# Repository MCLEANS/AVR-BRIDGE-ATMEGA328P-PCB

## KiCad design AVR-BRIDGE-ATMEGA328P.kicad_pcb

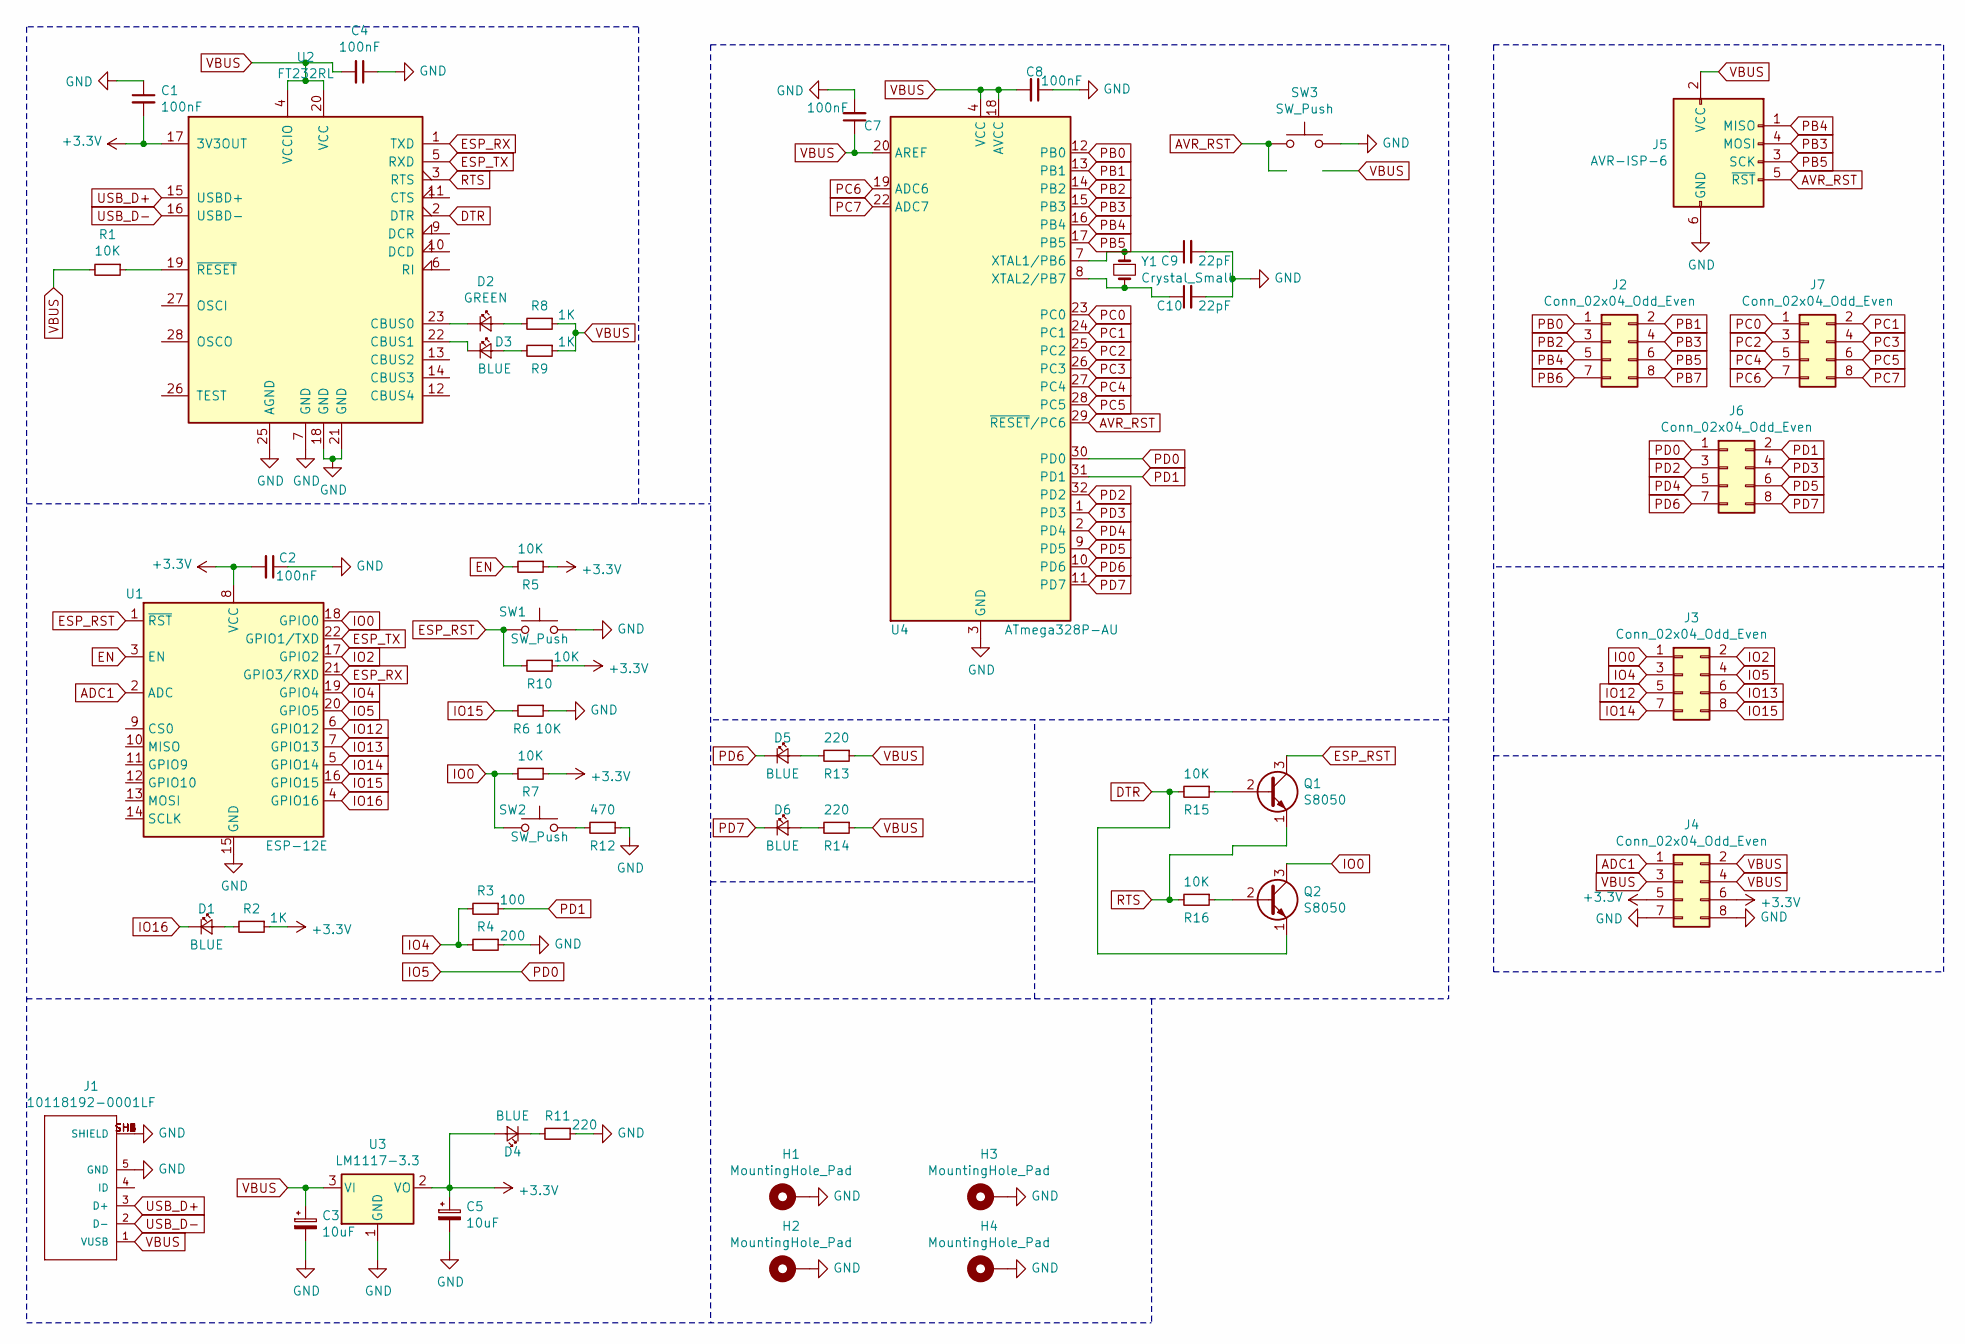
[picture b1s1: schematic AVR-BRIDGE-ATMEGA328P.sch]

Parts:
C1, C2, C4, C7, C8: 100nF; C_0805_2012Metric
C3, C5: 10uF; CP_Elec_4x5.3
C9, C10: 22pF; C_0805_2012Metric
D1, D3, D4, D5, D6: BLUE; LED_0805_2012Metric
D2: GREEN; LED_0805_2012Metric
H1, H2, H3, H4: MountingHole_Pad; MountingHole_2.7mm_Pad_Via
J1: 10118192-0001LF; AMPHENOL_10118192-0001LF
J2, J3, J4, J6, J7: Conn_02x04_Odd_Even; PinHeader_2x04_P2.54mm_Horizontal
J5: AVR-ISP-6; PinHeader_2x03_P2.54mm_Vertical
Q1, Q2: S8050; SOT-23-3
R1, R5, R6, R7, R10, R15, R16: 10K; R_0805_2012Metric
R2, R8, R9: 1K; R_0805_2012Metric
R3: 100; R_0805_2012Metric
R4: 200; R_0805_2012Metric
R11, R13, R14: 220; R_0805_2012Metric
R12: 470; R_0805_2012Metric
SW1, SW2, SW3: SW_Push; Switch_Tactile_SMD_6x6mm_PTS645
U1: ESP-12E
U2: FT232RL; SSOP-28_5.3x10.2mm_P0.65mm
U3: LM1117-3.3; SOT-223
U4: ATmega328P-AU; TQFP-32_7x7mm_P0.8mm
Y1: Crystal_Small; Crystal_SMD_HC49-SD

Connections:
+3V3: C1.2, C2.2, C5.1, D4.2 (A), J4.5, J4.6, R2.1, R5.1, R7.1, R10.1, U1.8 (VCC), U2.17 (3V3OUT), U3.2 (VO)
ADC1: J4.1, U1.2 (ADC)
AVR_RST: J5.5 (~RST), SW3.1, U4.29 (~RESET~/PC6)
DTR: Q2.1 (E), R15.2, U2.2 (DTR)
EN: R5.2, U1.3 (EN)
ESP_RST: Q1.3 (C), R10.2, SW1.1, U1.1 (~RST)
ESP_RX: U1.21 (GPIO3/RXD), U2.1 (TXD)
ESP_TX: U1.22 (GPIO1/TXD), U2.5 (RXD)
GND: C1.1, C2.1, C3.2, C4.1, C5.2, C7.2, C8.1, C9.2, C10.2, H1.1, H2.1, H3.1, H4.1, J1.5 (GND), J1.SH1 (SHIELD), J1.SH2 (SHIELD), J1.SH3 (SHIELD), J1.SH4 (SHIELD), J1.SH5 (SHIELD), J1.SH6 (SHIELD), J4.7, J4.8, J5.6 (GND), R4.1, R6.1, R11.1, R12.1, SW1.2, SW3.2, U1.15 (GND), U2.7 (GND), U2.18 (GND), U2.21 (GND), U2.25 (AGND), U3.1 (GND), U4.3 (GND), U4.5 (GND), U4.21 (GND)
IO0: J3.1, Q2.3 (C), R7.2, SW2.1, U1.18 (GPIO0)
IO2: J3.2, U1.17 (GPIO2)
IO4: J3.3, R3.2, R4.2, U1.19 (GPIO4)
IO5: J3.4, J6.1, U1.20 (GPIO5), U4.30 (PD0)
IO12: J3.5, U1.6 (GPIO12)
IO13: J3.6, U1.7 (GPIO13)
IO14: J3.7, U1.5 (GPIO14)
IO15: J3.8, R6.2, U1.16 (GPIO15)
IO16: D1.1 (K), U1.4 (GPIO16)
unnamed: C9.1, U4.7 (XTAL1/PB6), Y1.1
unnamed: C10.1, U4.8 (XTAL2/PB7), Y1.2
unnamed: D1.2 (A), R2.2
unnamed: D2.1 (K), U2.23 (CBUS0)
unnamed: D2.2 (A), R8.2
unnamed: D3.1 (K), U2.22 (CBUS1)
unnamed: D3.2 (A), R9.2
unnamed: D4.1 (K), R11.2
unnamed: D5.2 (A), R13.2
unnamed: D6.2 (A), R14.2
unnamed: Q1.2 (B), R15.1
unnamed: Q2.2 (B), R16.1
unnamed: R1.1, U2.19 (~RESET~)
unnamed: R12.2, SW2.2
PB0: J2.1, U4.12 (PB0)
PB1: J2.2, U4.13 (PB1)
PB2: J2.3, U4.14 (PB2)
PB3: J2.4, J5.4 (MOSI), U4.15 (PB3)
PB4: J2.5, J5.1 (MISO), U4.16 (PB4)
PB5: J2.6, J5.3 (SCK), U4.17 (PB5)
PB6: J2.7
PB7: J2.8
PC0: J7.1, U4.23 (PC0)
PC1: J7.2, U4.24 (PC1)
PC2: J7.3, U4.25 (PC2)
PC3: J7.4, U4.26 (PC3)
PC4: J7.5, U4.27 (PC4)
PC5: J7.6, U4.28 (PC5)
PC6: J7.7, U4.19 (ADC6)
PC7: J7.8, U4.22 (ADC7)
PD1: J6.2, R3.1, U4.31 (PD1)
PD2: J6.3, U4.32 (PD2)
PD3: J6.4, U4.1 (PD3)
PD4: J6.5, U4.2 (PD4)
PD5: J6.6, U4.9 (PD5)
PD6: D5.1 (K), J6.7, U4.10 (PD6)
PD7: D6.1 (K), J6.8, U4.11 (PD7)
RTS: Q1.1 (E), R16.2, U2.3 (RTS)
USB_D+: J1.3 (D+), U2.15 (USBD+)
USB_D-: J1.2 (D-), U2.16 (USBD-)
VBUS: C3.1, C4.2, C7.1, C8.2, J1.1 (VUSB), J4.2, J4.3, J4.4, J5.2 (VCC), R1.2, R8.1, R9.1, R13.1, R14.1, U2.4 (VCCIO), U2.20 (VCC), U3.3 (VI), U4.4 (VCC), U4.6 (VCC), U4.18 (AVCC), U4.20 (AREF)

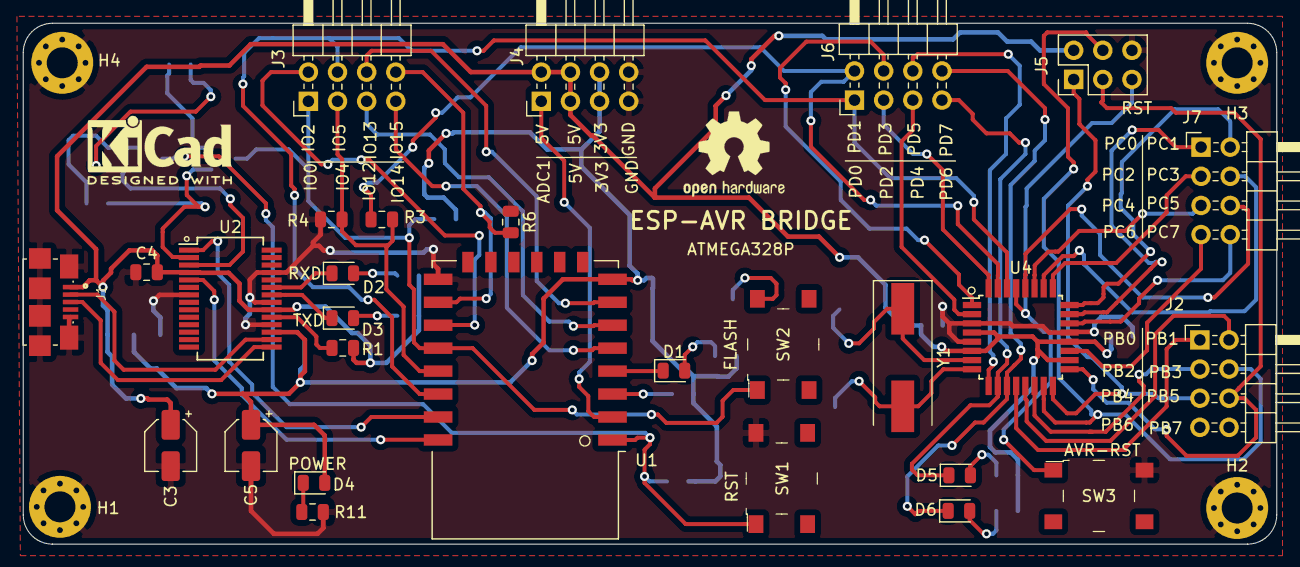
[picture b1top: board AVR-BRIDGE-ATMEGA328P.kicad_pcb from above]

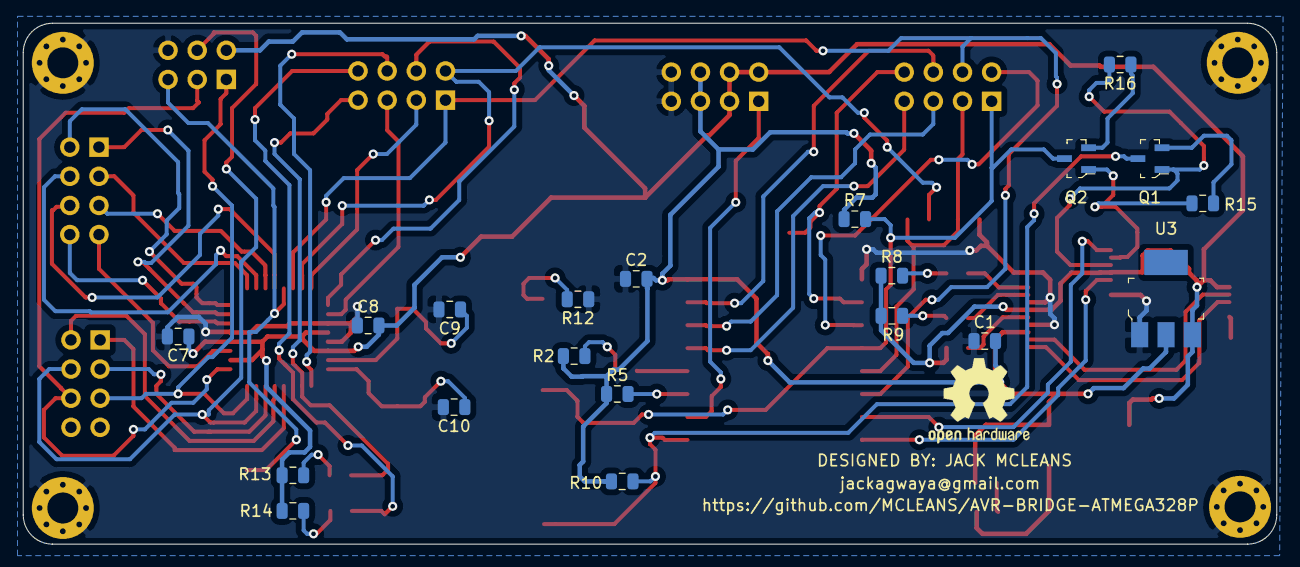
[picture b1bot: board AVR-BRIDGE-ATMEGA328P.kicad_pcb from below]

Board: 2 copper layers, 109.3 x 45.4 mm, 52 parts (20 on the bottom side), 57 nets.

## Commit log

2020-07-12 first iteration PCB design
